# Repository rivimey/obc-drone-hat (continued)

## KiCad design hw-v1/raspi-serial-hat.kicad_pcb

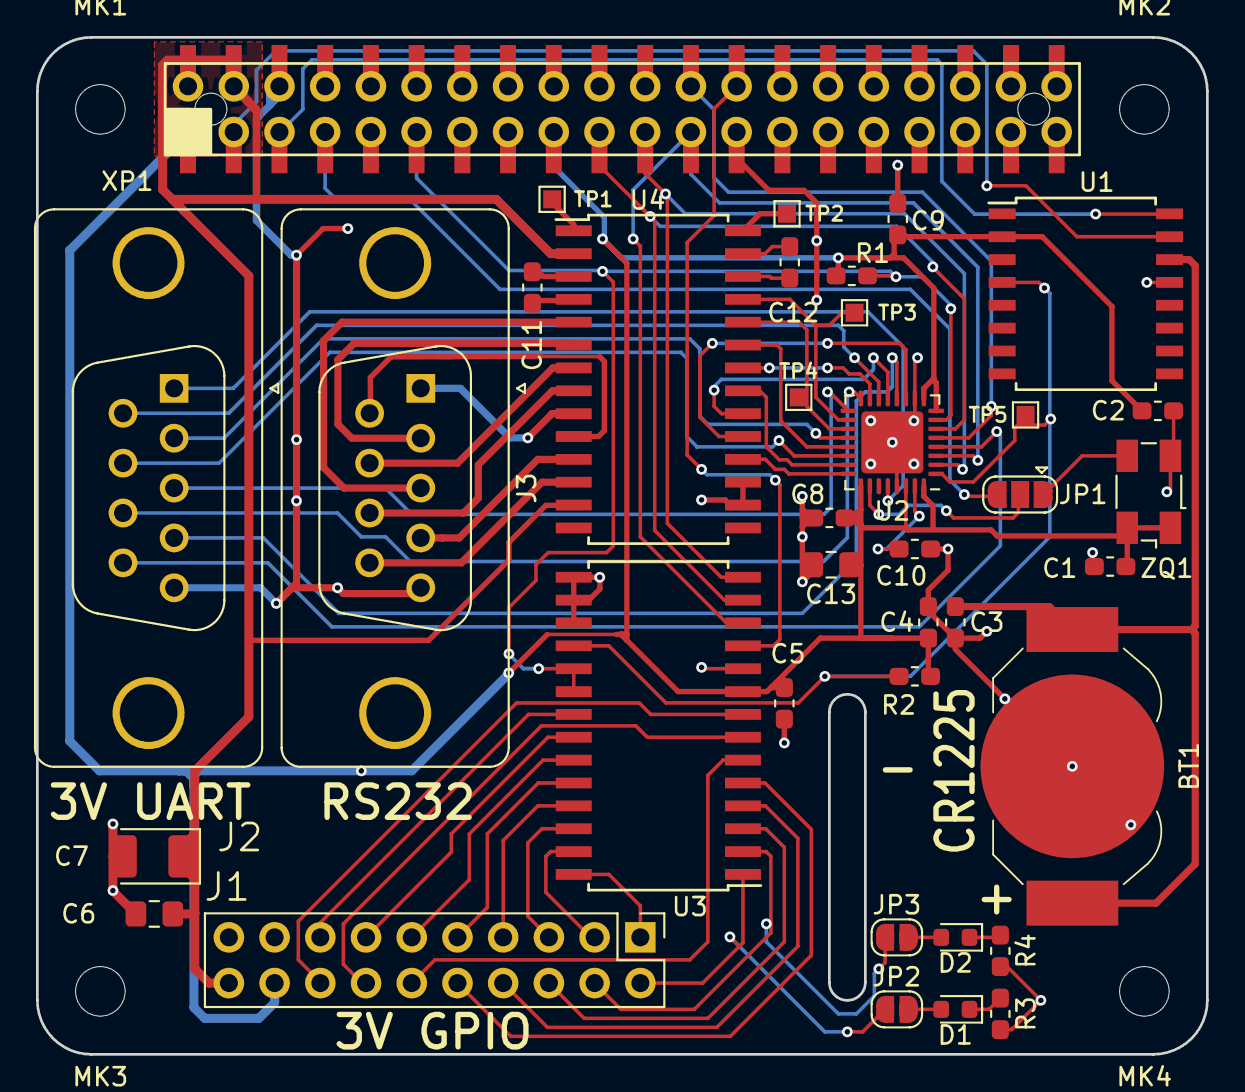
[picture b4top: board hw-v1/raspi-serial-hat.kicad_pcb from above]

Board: 2 copper layers, 65.0 x 56.5 mm, 41 parts (0 on the bottom side), 67 nets.

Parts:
BT1: CR1225; BatteryHolder_LINX_BAT-HLD-012-SMT
C1, C8, C9, C10: 100nF; C_0603_1608Metric_Pad1.05x0.95mm_HandSolder
C2, C4, C5: 1uF; C_0603_1608Metric_Pad1.05x0.95mm_HandSolder
C3: 470nF; C_0603_1608Metric_Pad1.05x0.95mm_HandSolder
C6, C13: 10uF Ceramic; C_0805_2012Metric_Pad1.15x1.40mm_HandSolder
C7: 100uF Tant; CP_EIA-3528-12_Kemet-T_Pad1.50x2.35mm_HandSolder
C11, C12: 0.1uF; C_0603_1608Metric_Pad1.05x0.95mm_HandSolder
D1, D2: LED; D_0603_1608Metric
J1: Conn_02x10_Odd_Even; PinHeader_2x10_P2.54mm_Vertical
J2, J3: DB9_Male; DSUB-9_Male_Vertical_P2.77x2.84mm_MountingHoles
JP1: CLK Source; SolderJumper-3_P1.3mm_Open_RoundedPad1.0x1.5mm
JP2: LED1 Enable; SolderJumper-2_P1.3mm_Open_RoundedPad1.0x1.5mm
JP3: LED2 Enable; SolderJumper-2_P1.3mm_Open_RoundedPad1.0x1.5mm
MK1, MK2, MK3, MK4: Mounting_Hole; M2.5_Mounting_Hole
R1: 10k; R_0603_1608Metric_Pad1.05x0.95mm_HandSolder
R2: nc; R_0603_1608Metric_Pad1.05x0.95mm_HandSolder
R3, R4: 470; R_0603_1608Metric_Pad1.05x0.95mm_HandSolder
TP1, TP2, TP3, TP4, TP5: TestPoint; TestPoint_Pad_1.0x1.0mm
U1: DS3231; SOIC-16W_7.5x10.3mm_P1.27mm
U2: MAX3109; QFN-32-1EP_5x5mm_P0.5mm_EP3.45x3.45mm
U3: MCP23S17; SOIC-28W_7.5x17.9mm_P1.27mm
U4: LT1137ACSW; SOIC-28W_7.5x17.9mm_P1.27mm
XP1: Rpi_40PIN; RaspberryPi-40Pin_P2.54mm
ZQ1: ASFL1-24.000MHZ-EC-T; Crystal_SMD_Abracon_ABM3B-4Pin_5.0x3.2mm

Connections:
+3V3: C1.1, C2.1, C4.1, C5.1, C8.1, C9.1, C13.1, J1.18, R1.2, R2.2, U1.2, U2.8, U2.9, U2.25, U2.30, U2.32, U3.9, XP1.1, XP1.17, ZQ1.1, ZQ1.4
+5V: C6.1, C7.1, J1.20, U4.2, U4.13, XP1.2, XP1.4
/+3Vbat: BT1.1, C3.1, U1.14
/CE0: U2.5, XP1.24
/CE1: U3.11, XP1.26
/E_CTS: J3.8, U4.8
/E_DCD: J3.1, U4.9
/E_DSR: J3.6, U4.10
/E_DTR: J3.4, U4.11
/E_RI: J3.9, U4.12
/E_RTS: J3.7, U4.7
/E_RX: J3.2, U4.6
/E_TX: J3.3, U4.5
/U0_RX: TP4.1, U2.19, U4.24
/U0_TX: TP3.1, U2.18, U4.25
/U1_RX: J2.2, U2.20
/U1_TX: J2.3, U2.17
/U_V18: C10.1, U2.31
/V+: TP1.1, U4.1
/V-: TP2.1, U4.28
/ZQ_CLK: JP1.1, ZQ1.3
/~U0_CTS: U2.15, U4.22
/~U0_DCD: U2.23, U4.21
/~U0_DSR: U2.13, U4.20
/~U0_DTR: U2.11, U4.19
/~U0_RI: U2.24, U4.18
/~U0_RTS: U2.21, U4.23
/~U1_CTS: J2.8, U2.16
/~U1_DCD: J2.1, U2.28
/~U1_DSR: J2.6, U2.14
/~U1_DTR: J2.4, U2.12
/~U1_RI: J2.9, U2.4
/~U1_RTS: J2.7, U2.22
GND: BT1.2, C1.2, C2.2, C3.2, C4.2, C5.2, C6.2, C7.2, C8.2, C9.2, C10.2, C13.2, J1.17, J1.19, J2.5, J3.5, R3.2, R4.2, U1.13, U2.10, U2.29, U2.33, U3.10, U3.15, U3.16, U3.17, U4.16, U4.17, XP1.6, XP1.9, XP1.14, XP1.20, XP1.25, XP1.30, XP1.34, XP1.39, ZQ1.2
HAT_CLK: JP1.2, U2.26
unnamed: C11.1, U4.3
unnamed: C11.2, U4.4
unnamed: C12.1, U4.26
unnamed: C12.2, U4.27
unnamed: D1.1, R3.1
unnamed: D1.2, JP2.2
unnamed: D2.1, R4.1
unnamed: D2.2, JP3.2
unnamed: J1.1, U3.28
unnamed: J1.2, JP2.1, U3.1
unnamed: J1.3, U3.27
unnamed: J1.4, JP3.1, U3.2
unnamed: J1.5, U3.26
unnamed: J1.6, U3.3
unnamed: J1.7, U3.25
unnamed: J1.8, U3.4
unnamed: J1.9, U3.24
unnamed: J1.10, U3.5
unnamed: J1.11, U3.23
unnamed: J1.12, U3.6
unnamed: J1.13, U3.22
unnamed: J1.14, U3.7
unnamed: J1.15, U3.21
unnamed: J1.16, U3.8
RPI_GPCLK0: JP1.3, XP1.7
RPI_SCL: U1.16, XP1.5
RPI_SDA: U1.15, XP1.3
RPI_SPI0_MISO: U2.2, U3.14, XP1.21
RPI_SPI0_MOSI: U2.6, U3.13, XP1.19
RPI_SPI0_SCLK: U2.3, U3.12, XP1.23
~HAT_RST: R2.1, TP5.1, U1.4, U2.1, U3.18
~SER_IRQ_A: R1.1, U2.7, U3.19, U3.20, XP1.11

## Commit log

2019-02-19 rebuild as serio/pario hat
2019-03-01 prepare for v2
2019-03-28 board v2, using IDC cables and with config rom.
2019-10-09 Version 3
2019-10-09 Tidy folder
2019-11-05 Create gerbers and relabel schematic
